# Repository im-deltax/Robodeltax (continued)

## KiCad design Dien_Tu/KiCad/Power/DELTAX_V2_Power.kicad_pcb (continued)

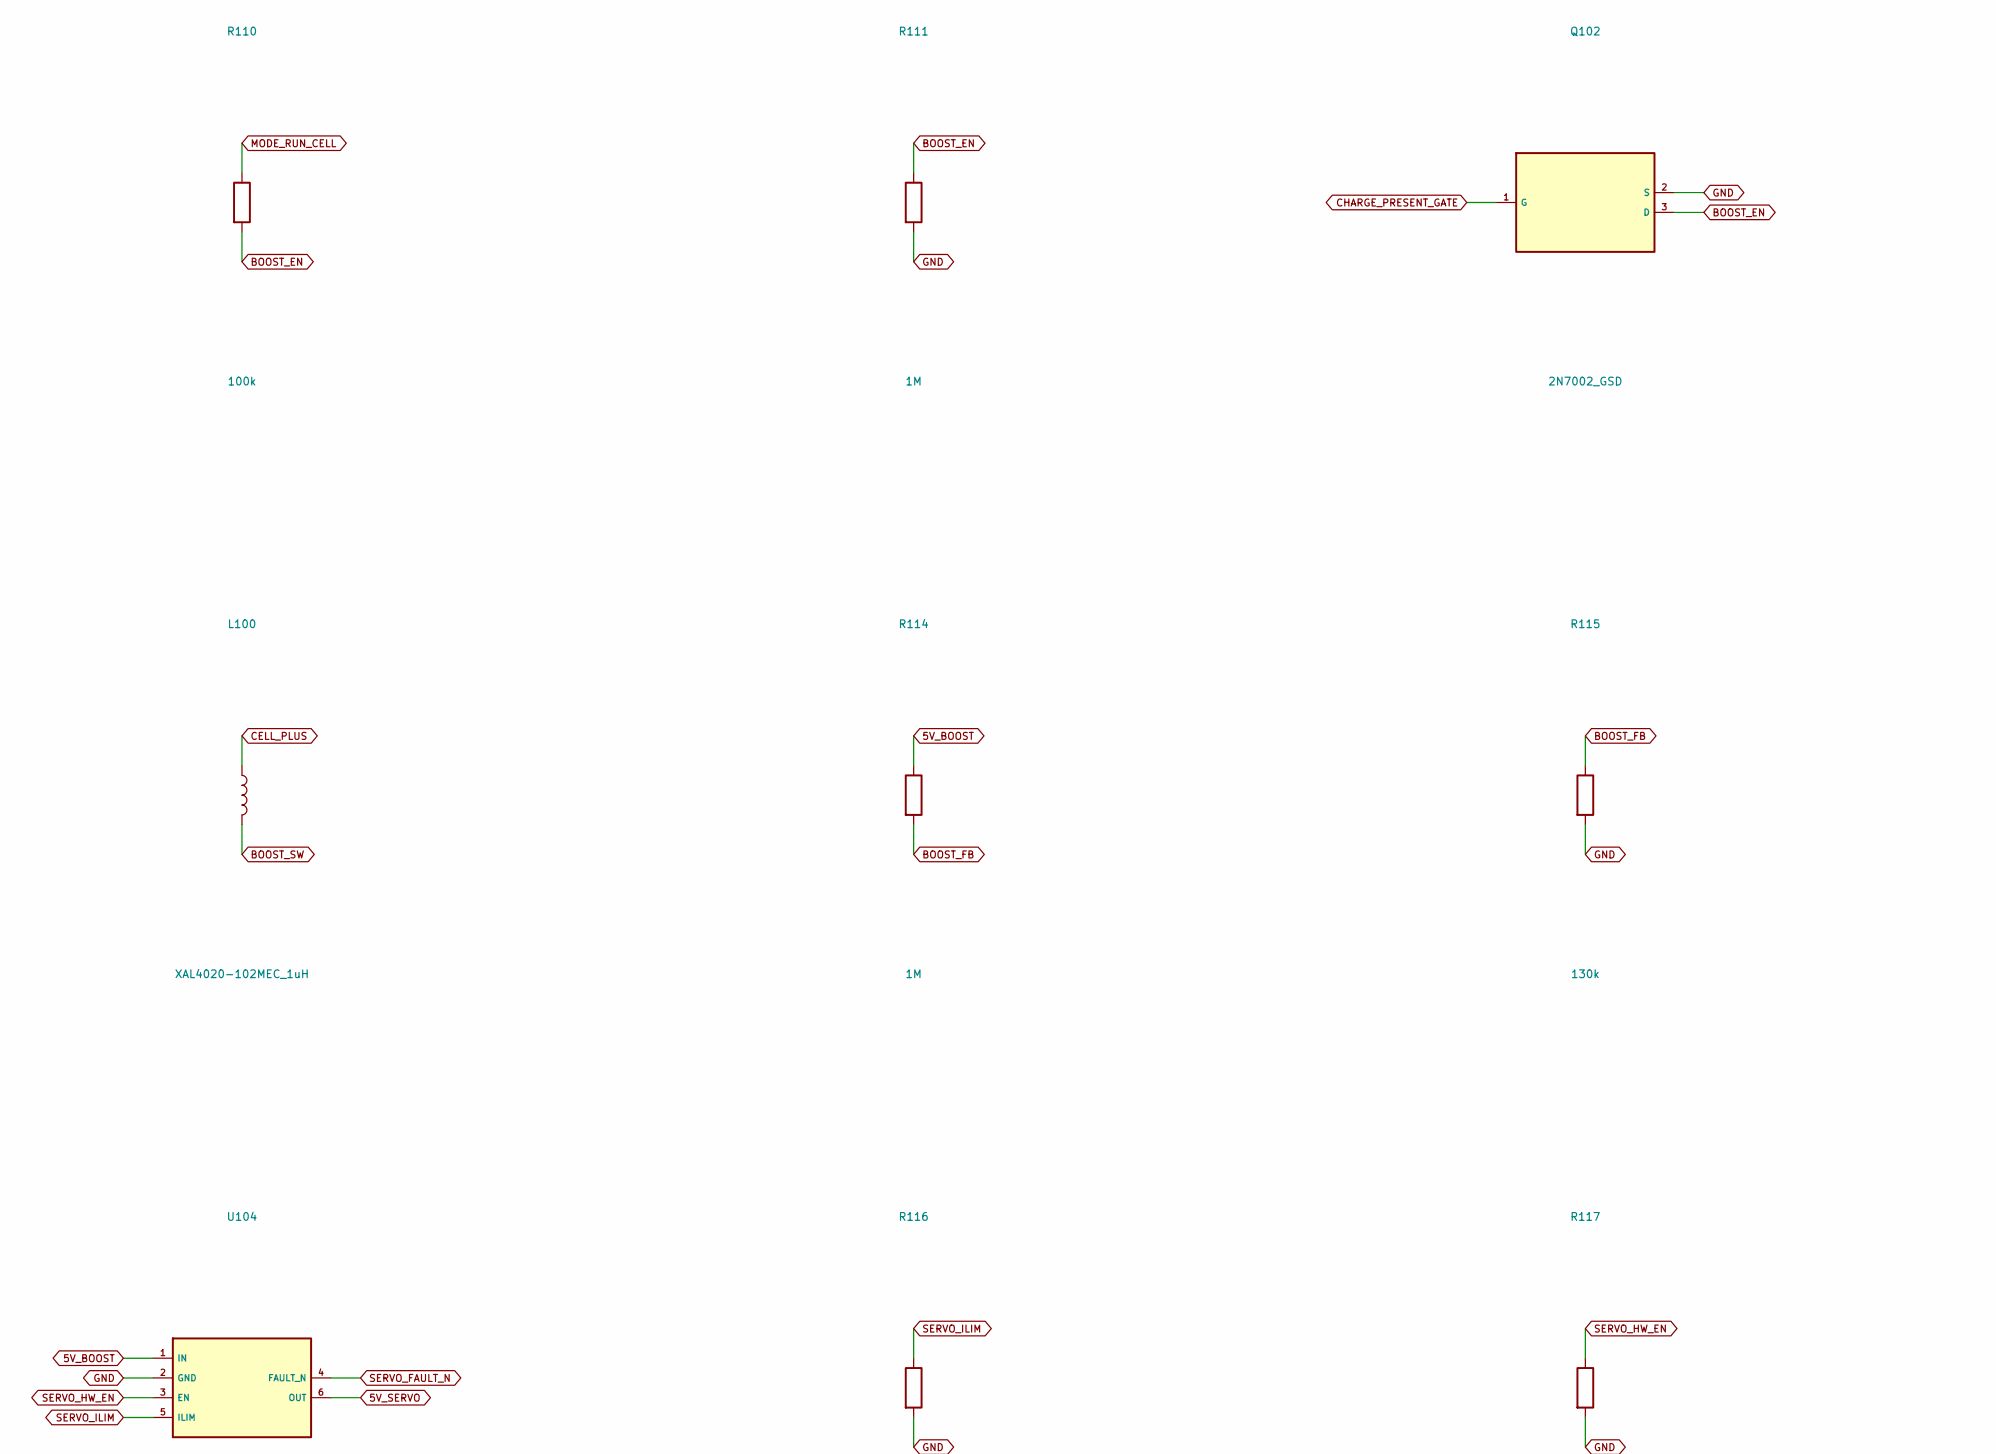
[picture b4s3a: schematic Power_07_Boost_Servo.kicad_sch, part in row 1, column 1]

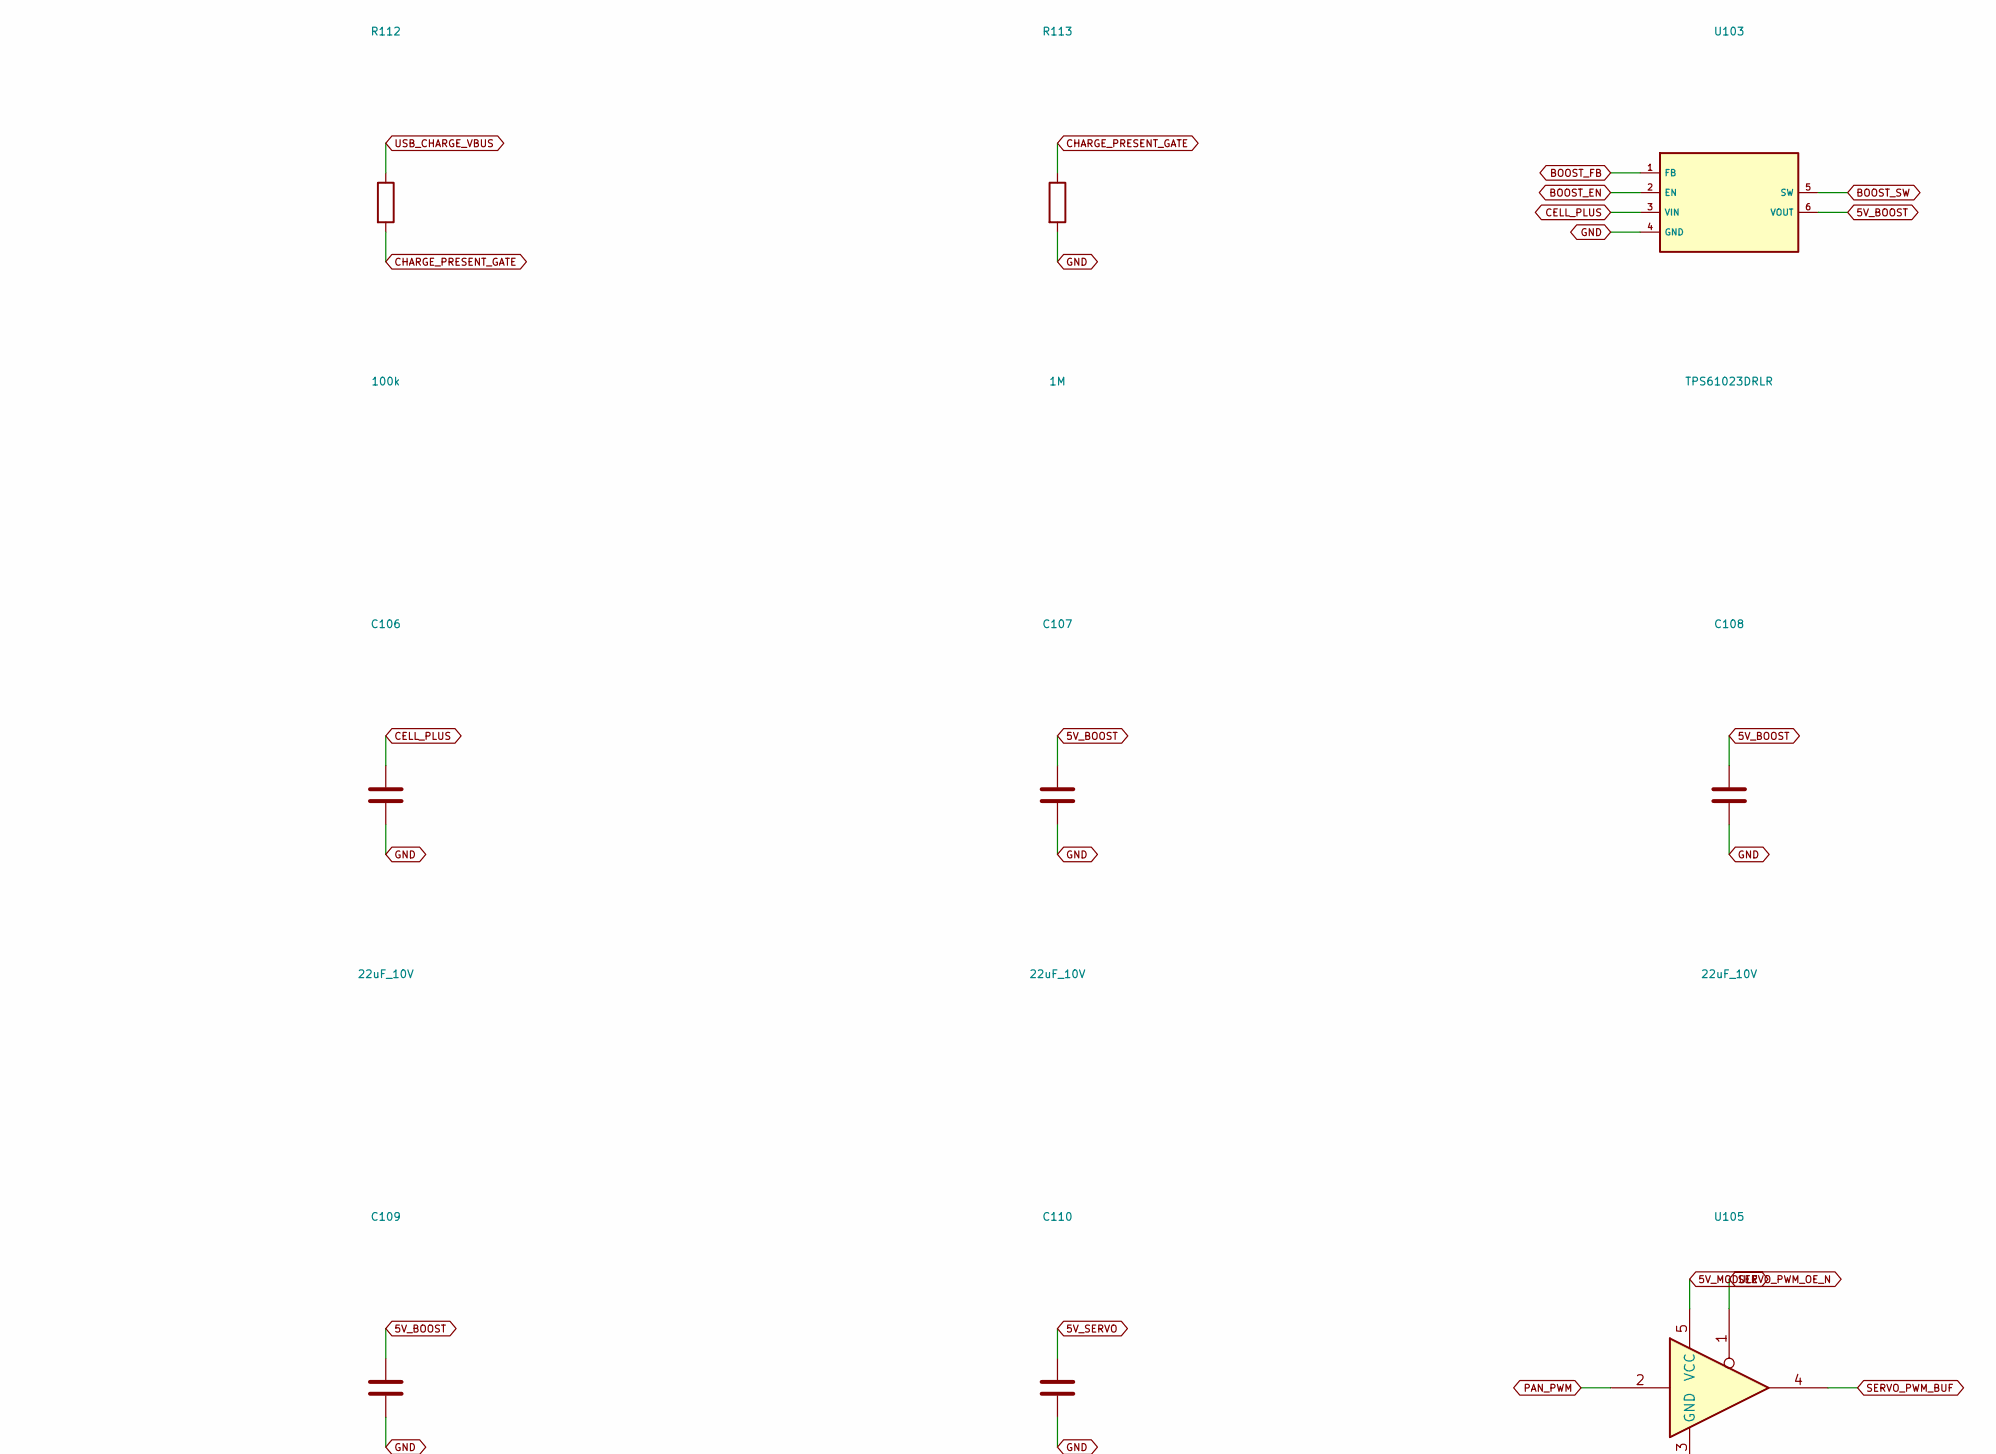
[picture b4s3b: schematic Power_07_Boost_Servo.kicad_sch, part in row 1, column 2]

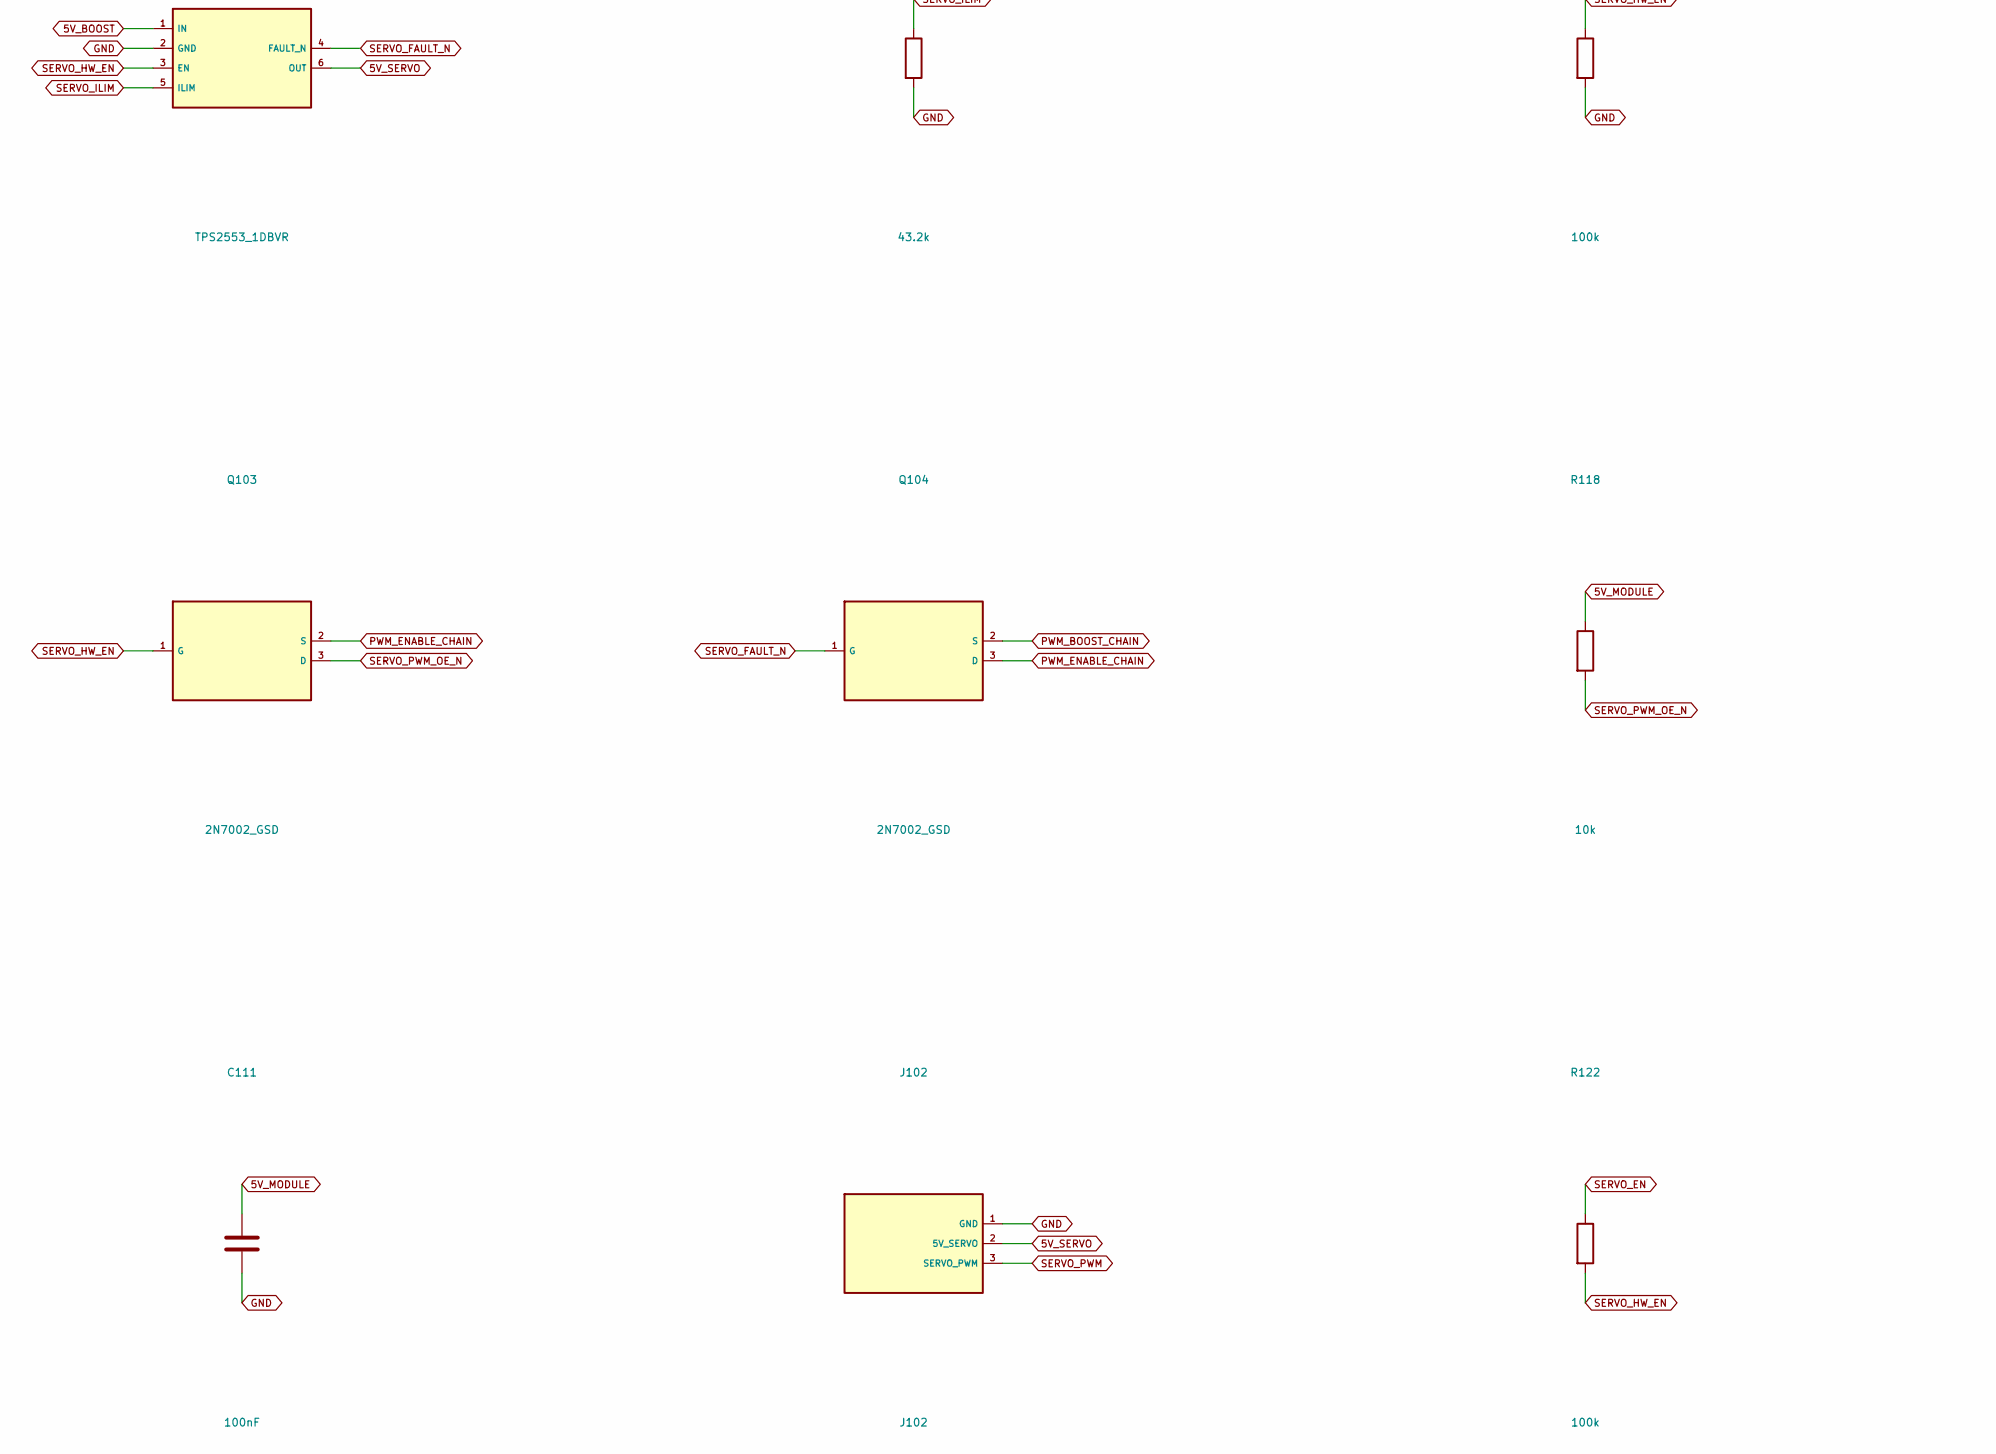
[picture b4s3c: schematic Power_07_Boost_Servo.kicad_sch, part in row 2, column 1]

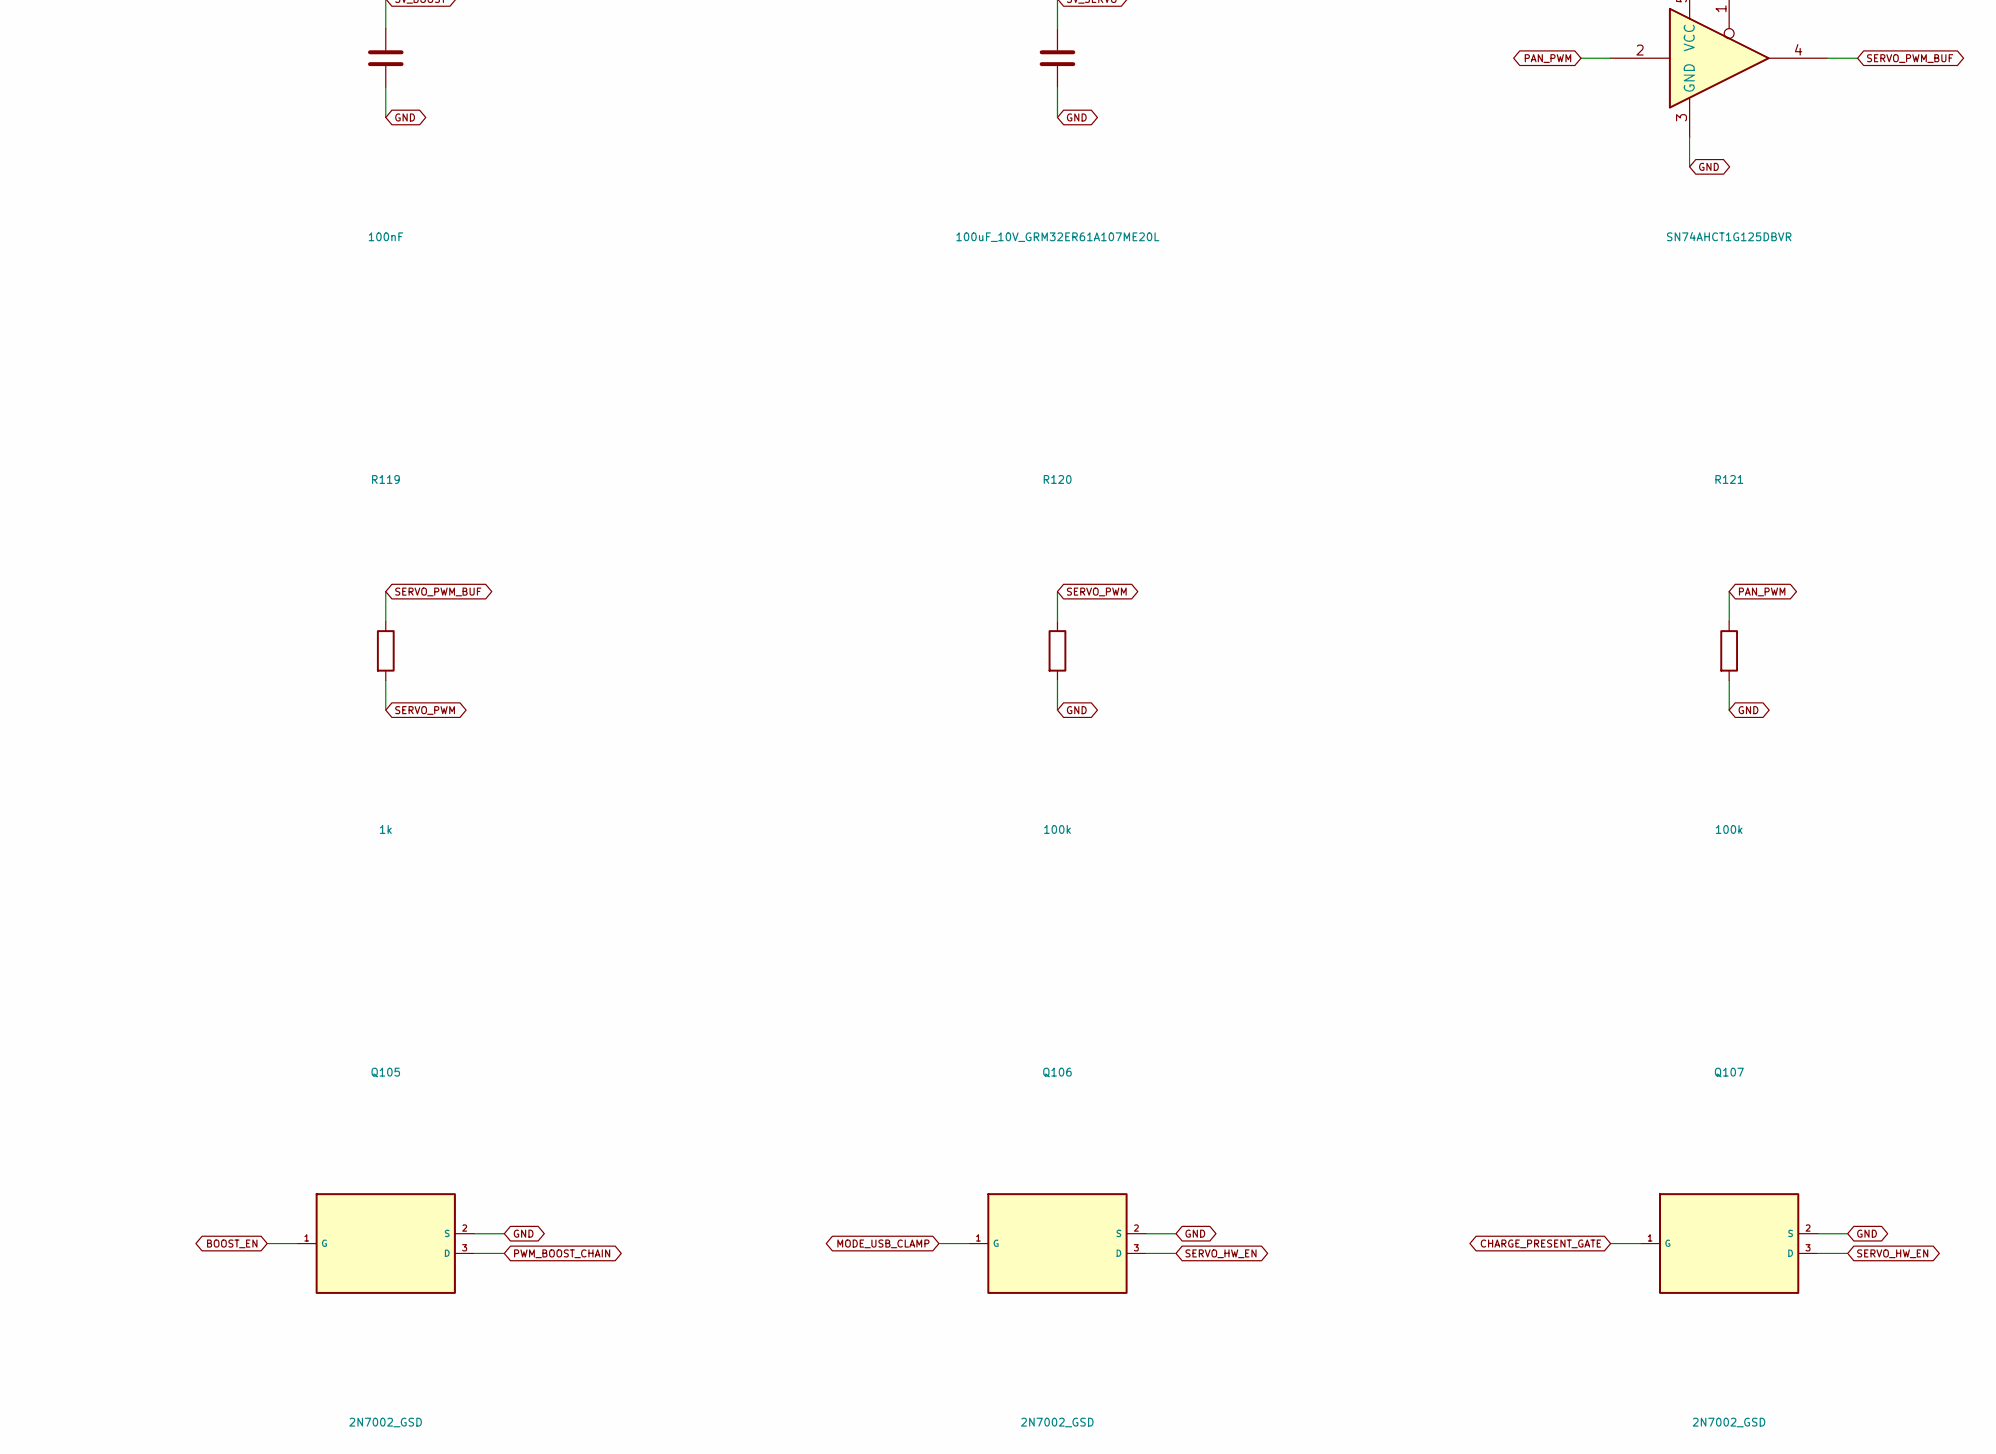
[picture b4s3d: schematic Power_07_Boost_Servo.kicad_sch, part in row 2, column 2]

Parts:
C106, C107, C108: 22uF_10V; C_0805_2012Metric
C109: 100nF; C_0603_1608Metric
C110: 100uF_10V_GRM32ER61A107ME20L; C_1210_3225Metric
C111: 100nF; C_0402_1005Metric
J102: J102; PowerPads_3
L100: XAL4020-102MEC_1uH; L_Coilcraft_XAL4020-XXX
Q102, Q103, Q104, Q105, Q106, Q107: 2N7002_GSD; SOT-23
R110, R112, R117, R120, R121, R122: 100k; R_0603_1608Metric
R111, R113, R114: 1M; R_0603_1608Metric
R115: 130k; R_0603_1608Metric
R116: 43.2k; R_0603_1608Metric
R118: 10k; R_0603_1608Metric
R119: 1k; R_0603_1608Metric
U103: TPS61023DRLR; SOT-563
U104: TPS2553_1DBVR; SOT-23-6
U105: SN74AHCT1G125DBVR; SOT-23-5

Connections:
5V_BOOST: C107.1, C108.1, C109.1, R114.1, U103.6 (VOUT), U104.1 (IN); also elsewhere on the board
5V_MODULE: C111.1, R118.1, U105.5 (VCC); also elsewhere on the board
5V_SERVO: C110.1, J102.2 (5V_SERVO), U104.6 (OUT)
BOOST_EN: Q102.3 (D), Q105.1 (G), R110.2, R111.1, U103.2 (EN); also elsewhere on the board
BOOST_FB: R114.2, R115.1, U103.1 (FB)
BOOST_SW: L100.2, U103.5 (SW)
CELL_PLUS: C106.1, L100.1, U103.3 (VIN); also elsewhere on the board
CHARGE_PRESENT_GATE: Q102.1 (G), Q107.1 (G), R112.2, R113.1
GND: C106.2, C107.2, C108.2, C109.2, C110.2, C111.2, J102.1 (GND), Q102.2 (S), Q105.2 (S), Q106.2 (S), Q107.2 (S), R111.2, R113.2, R115.2, R116.2, R117.2, R120.2, R121.2, U103.4 (GND), U104.2 (GND), U105.3 (GND); also elsewhere on the board
MODE_RUN_CELL: R110.1; also elsewhere on the board
MODE_USB_CLAMP: Q106.1 (G); also elsewhere on the board
PAN_PWM: R121.1, U105.2; also elsewhere on the board
PWM_BOOST_CHAIN: Q104.2 (S), Q105.3 (D)
PWM_ENABLE_CHAIN: Q103.2 (S), Q104.3 (D)
SERVO_EN: R122.1; also elsewhere on the board
SERVO_FAULT_N: Q104.1 (G), U104.4 (FAULT_N); also elsewhere on the board
SERVO_HW_EN: Q103.1 (G), Q106.3 (D), Q107.3 (D), R117.1, R122.2, U104.3 (EN)
SERVO_ILIM: R116.1, U104.5 (ILIM)
SERVO_PWM: J102.3 (SERVO_PWM), R119.2, R120.1
SERVO_PWM_BUF: R119.1, U105.4
SERVO_PWM_OE_N: Q103.3 (D), R118.2, U105.1
USB_CHARGE_VBUS: R112.1; also elsewhere on the board

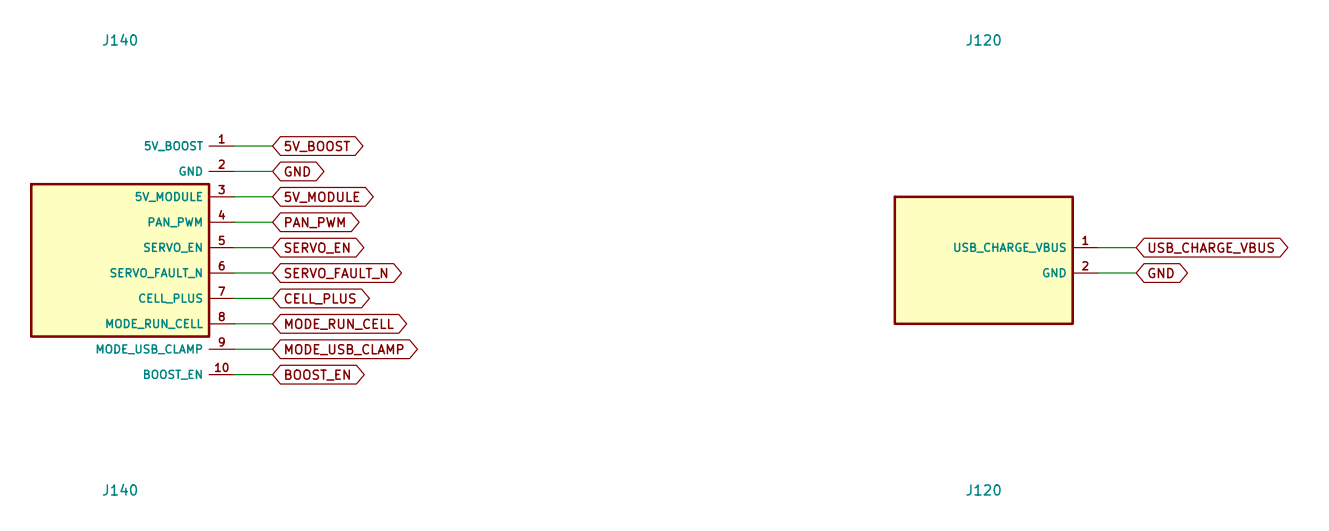
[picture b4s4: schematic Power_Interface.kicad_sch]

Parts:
J120: J120; PowerPads_2
J140: J140; PowerPads_10

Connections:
5V_BOOST: J140.1 (5V_BOOST); also elsewhere on the board
5V_MODULE: J140.3 (5V_MODULE); also elsewhere on the board
BOOST_EN: J140.10 (BOOST_EN); also elsewhere on the board
CELL_PLUS: J140.7 (CELL_PLUS); also elsewhere on the board
GND: J120.2 (GND), J140.2 (GND); also elsewhere on the board
MODE_RUN_CELL: J140.8 (MODE_RUN_CELL); also elsewhere on the board
MODE_USB_CLAMP: J140.9 (MODE_USB_CLAMP); also elsewhere on the board
PAN_PWM: J140.4 (PAN_PWM); also elsewhere on the board
SERVO_EN: J140.5 (SERVO_EN); also elsewhere on the board
SERVO_FAULT_N: J140.6 (SERVO_FAULT_N); also elsewhere on the board
USB_CHARGE_VBUS: J120.1 (USB_CHARGE_VBUS); also elsewhere on the board

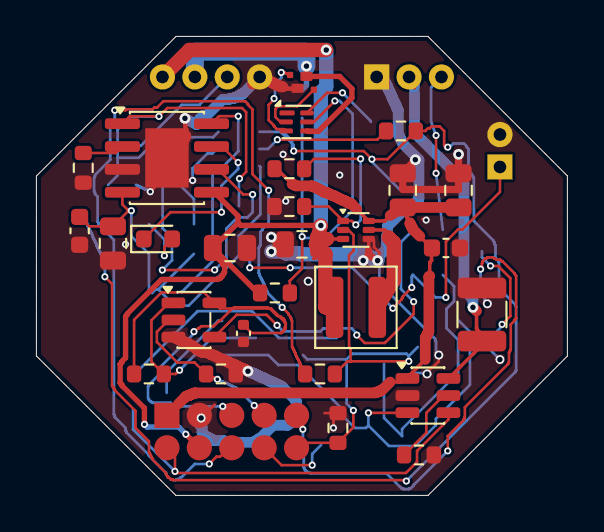
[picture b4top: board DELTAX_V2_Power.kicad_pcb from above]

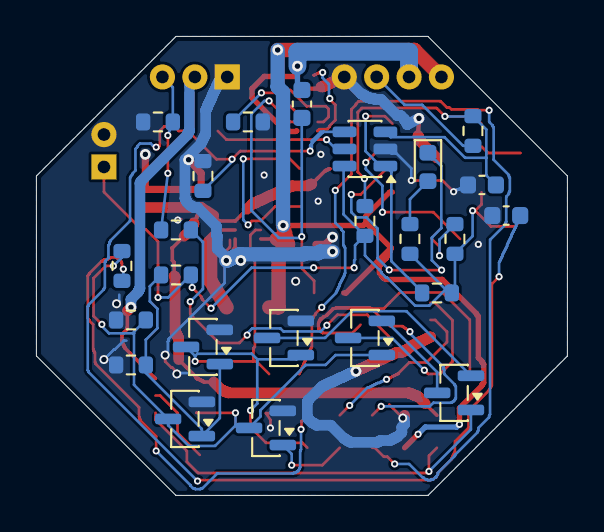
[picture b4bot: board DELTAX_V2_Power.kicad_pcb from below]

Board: 2 copper layers, 29.5 x 25.5 mm, 55 parts (24 on the bottom side), 37 nets.
